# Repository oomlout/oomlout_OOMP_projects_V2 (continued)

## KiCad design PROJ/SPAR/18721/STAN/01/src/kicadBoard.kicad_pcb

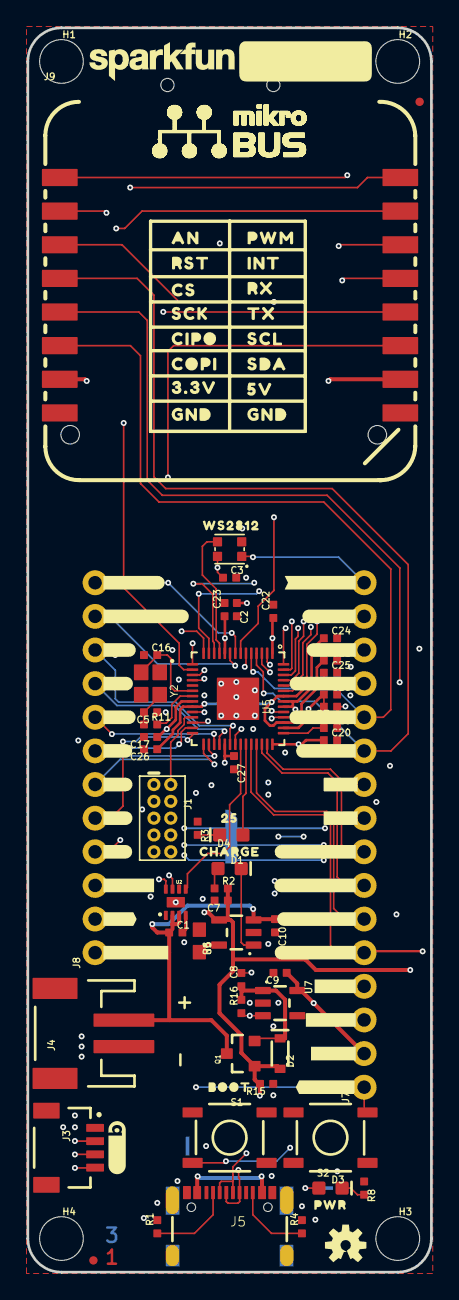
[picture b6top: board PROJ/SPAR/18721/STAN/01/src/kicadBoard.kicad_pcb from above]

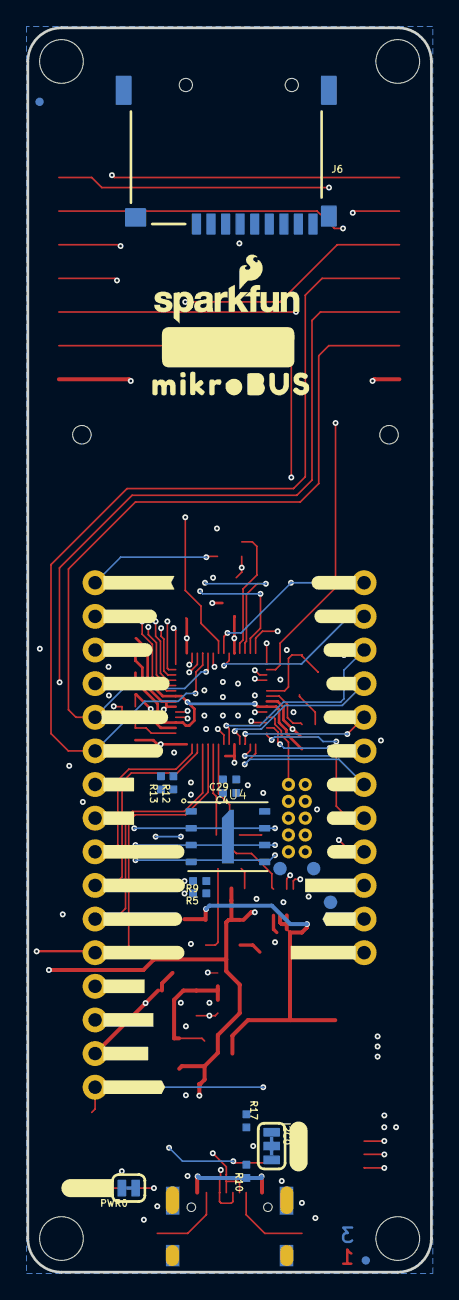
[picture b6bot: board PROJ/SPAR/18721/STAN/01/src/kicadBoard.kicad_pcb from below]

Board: 4 copper layers, 30.5 x 94.0 mm, 161 parts (50 on the bottom side), 65 nets.

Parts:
C1, C2, C3, C17, C18, C20, C21, C22, C23, C24, C25, C29: 0.1uF; 0402-TIGHT
C4, C9, C26, C27, C28: 2.2uF; 0402-TIGHT
C5, C16: 15pF; 0402-TIGHT
C7, C10: 4.7uF; 0402-TIGHT
C8: 1.0uF; 0402-TIGHT
D1: Yellow; LED-0603
D2: 1A/23V/620mV; SOD-323
D3: RED; LED-0603
D4: BLUE; LED-0603
D5: WS2812_2020; WS2812-2020
FD1, FD2, FD3, FD4: FIDUCIALUFIDUCIAL; FIDUCIAL-MICRO
FRAME1: FRAME-LEDGER; CREATIVE_COMMONS
H1, H2, H3, H4: STAND-OFF
I2C0: JUMPER-SMT_3_2-NC_TRACE_SILK; SMT-JUMPER_3_2-NC_TRACE_SILK
J1: SWD; 2X5-PTH-1.27MM
J3: Qwiic; JST04_1MM_RA
J4: JST-2-SMD
J5: USB C; USB-C-16P-4LAYER-ISOLATED
J6: microSD; MICROSD-EXTERNALPIN
J7: 1X16_NO_SILK
J8: 1X12_NO_SILK
J9: MIKROBUS_SMD_BLACK1; MIKROBUS_SMD_BLACK
LOGO1: OSHW-LOGOS; OSHW-LOGO-S
LOGO2: SFE_LOGO_NAME.1_INCH; SFE_LOGO_NAME_.1
PWR0: JUMPER-SMT_2_NC_TRACE_SILK; SMT-JUMPER_2_NC_TRACE_SILK
Q1: 20V/4.2A/52mΩ/1.4W; SOT23-3
R1, R4: 5.1k; 0402-TIGHT
R2, R3, R5, R8, R11: 1k; 0402-TIGHT
R6: 2.0k; 0603
R7: 200OHM-0402T-1/16W-1%; 0402-TIGHT
R9, R15, R16: 10k; 0402-TIGHT
R10, R17: 2.2k; 0402-TIGHT
R12, R13: 27; 0402-TIGHT
S1, S2: MOMENTARY-SWITCH-SPST-SMD-5.2MM-TALL; TACTILE_SWITCH_SMD_5.2MM
TP1, TP2, TP3: TEST-POINT3X4; PAD.03X.04
U2: MAX17048; DFN-8
U3: MCP73831; SOT23-5
U4: W25QXX128MBIT; WSON-8-6X5-SKINNY_CENTERPAD
U5: RP2040; QFN-56
U7: 3.3V; SOT23-5
U$1: #_16#0
U$2: #_17#0
U$3: #_18#0
U$4: #_19#0
U$5: #_20#0
U$6: #_21#0
U$7: #_22#0
U$8: #_SCL#7#23#0
U$9: #_SDA#6#0
U$10: #WS2812_#0
U$11: #0#TX_#0
U$12: #1#RX_#0
U$13: #4#CIPO_#0
U$14: #3#COPI_#0
U$15: #2#SCK_#0
U$16: PWR0
U$17, U$73: RASPI_RP2040_LOGO_10MM
U$18: #29#ADC3_#0
U$19: #28#ADC2_#0
U$20: #27#ADC1_#0
U$21: #26#ADC0_#0
U$22: #_VUSB#0
U$23: #_EN#0
U$24: #_VBATT#0
U$25: #GND_#0
U$26: #AREF_#0
U$27: #3#3V_#0
U$28: ##RESET##0
U$29: AN0
U$30: WS28120
U$31: ORDERING_INSTRUCTIONS
U$32: SFE_LOGO_NAME_FLAME_.1
U$33: #SCL_#0
U$34: #SDA_#0
U$35: #_#RESET##0
U$36: #_3#3V#0
U$37: #_AREF#0
U$38: #_GND#0
U$39: #_26#ADC0#0
U$40: #_27#ADC1#0
U$41: #_28#ADC2#0
U$42: #_29#ADC3#0
U$43: #LED#0
U$44: RST0
U$45: CS0
U$47, U$48: #_NC_#0
U$49: #_2#SCK#0
U$50: #_3#COPI#0
U$51: #_4#CIPO#0
U$52: #_1#RX#0
U$53: #_0#TX#0
U$54: 250
U$55: CHARGE0
U$56: BOOT0
U$57: #22_#0
U$58: #21_#0
U$59: #20_#0
U$60: CIPO0
U$61: #19_#0
U$62: #18_#0
U$63: #17_#0
U$64: QWIIC_4MM
U$65: #16_#0
U$66: #VUSB_#0
U$67: #EN_#0
U$68: #VBATT_#0
U$69, U$70: #_NC#0
U$71: #_WS2812#0
U$72: #I2C#0
U$74: SCK0
U$75: COPI0
U$76: 3#3V0
U$77, U$78: GND0
U$79: 5V0
U$80: SDA0
U$81: SCL0
U$82: TX0
U$83: RX0
U$84: INT0
U$85: PWM0
U$88: MIKROBUS0
Y2: 12MHz; CRYSTAL-SMD-2X2.5MM

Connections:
1.1V: C24.1, C25.1, C26.1, U5.23, U5.45, U5.50
3.3V: C2.1, C3.1, C4.1, C9.1, C17.1, C18.1, C20.1, C21.1, C22.1, C23.1, C27.1, C29.1, D5.VCC, I2C0.2, J1.1, J3.2, J6.4, J7.2, J9.7, PWR0.2, R7.2, R9.2, U4.8, U5.1, U5.10, U5.22, U5.33, U5.42, U5.44, U5.48, U5.49, U7.5
ADC0: J7.5, J9.1, U5.38
ADC1: J7.6, U5.39
ADC2: J7.7, U5.40
ADC3: J7.8, U5.41
AVDD: C28.1, J7.3, R7.1, U5.43
EN: J8.2, R16.1, U7.3
GND: C1.2, C2.2, C3.2, C4.2, C5.1, C7.2, C8.2, C9.2, C10.2, C16.1, C17.2, C18.2, C20.2, C21.2, C22.2, C23.2, C24.2, C25.2, C26.2, C27.2, C28.2, C29.2, D5.GND, J1.3, J1.5, J1.9, J3.1, J4.1, J5.GND, J5.GND2, J6.6, J6.9, J6.10, J6.11, J6.12, J6.13, J7.4, J9.8, J9.9, R1.2, R3.1, R4.2, R6.1, R8.1, R15.1, S1.1, S2.1, U2.1, U2.4, U2.6, U2.9, U3.2, U4.4, U5.19, U5.EPAD, U7.2
GPIO13: J9.2, U5.16
GPIO16: J8.4, J9.16, U5.27
GPIO17: J8.5, J9.15, U5.28
GPIO18: J8.6, U5.29
GPIO19: J8.7, U5.30
GPIO20: J8.8, U5.31
GPIO21: J8.9, U5.32
GPIO22: J8.10, U5.34
I2C1_SCL/GPIO23: J3.4, J8.11, J9.12, R10.1, U2.7, U5.9, U5.35
I2C1_SDA: J3.3, J8.12, J9.11, R17.1, U2.8, U5.8
LED_BUILTIN: D4.A, U5.37
unnamed: D4.C, R3.2
unnamed: I2C0.3, R10.2
unnamed: I2C0.1, R17.2
unnamed: R11.2, U5.21
unnamed: C16.2, U5.20, Y2.P3
unnamed: C5.2, R11.1, Y2.P1
unnamed: D3.C, R8.2
unnamed: D1.C, U3.1
unnamed: D3.A, PWR0.1
unnamed: J5.A5, R1.1
unnamed: J5.B5, R4.1
unnamed: R6.2, U3.5
unnamed: C8.1, D2.C, Q1.2, R16.2, U7.1
unnamed: D1.A, R2.1
QSPI-0: U4.5, U5.53
QSPI-1: U4.2, U5.55
QSPI-2: U4.3, U5.54
QSPI-3: U4.7, U5.51
QSPI-CLK: U4.6, U5.52
SDIO_DAT1: J6.8, U5.14
SDIO_DAT2: J6.1, U5.13
SPI0_CIPO: J7.13, J9.5, U5.6
SPI0_COPI: J7.12, J9.6, U5.5
SPI0_SCK: J7.11, J9.4, U5.4
SPI_CIPO1/SDIO_DAT0: J6.7, U5.15
SPI_COPI1/SDIO_CMD: J6.3, U5.18
SPI_SCK1/SDIO_CLK: J6.5, U5.17
SPI_~CS1/SDIO_DAT3: J6.2, U5.12
SWDCK: J1.4, TP1.1, U5.24
SWDIO: J1.2, TP2.1, U5.25
UART0_RX: J7.14, J9.14, U5.3
UART0_TX: J7.15, J9.13, U5.2
USB_F_N: R12.2, U5.46
USB_F_P: R13.2, U5.47
USB_N: J5.A7, J5.B7, R12.1
USB_P: J5.A6, J5.B6, R13.1
V_BATT: C1.1, C10.1, J4.2, J8.1, Q1.3, U2.2, U2.3, U3.3
V_USB: C7.1, D2.A, J5.VBUS1, J5.VBUS2, J8.3, J9.10, Q1.1, R2.2, R15.2, U3.4
WS2812_DI: D5.DI, U5.11
WS2812_DO: D5.DO, J7.16
~BATT_ALERT: U2.5, U5.36
~BOOT: R5.2, S1.3
~QSPI-CS: R5.1, R9.1, U4.1, U5.56
~RESET: J1.10, J7.1, S2.3, TP3.1, U5.26
~SPI0_CS: J9.3, U5.7
